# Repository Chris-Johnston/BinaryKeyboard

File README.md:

# BinaryKeyboard
A two-button backlit mechanical keyboard that types ASCII values, one bit at a time.

## Photos

## GIFS

Typing the backspace character, followed by switching between modes.

Demonstrating left to right input.

New animations added to '1/0' mode. (Still working on a name for that).

Demonstrating compatibility with USB OTG.

Boot up sequence.

Demonstrating right to left input.

Demonstrating switching between typing modes.

Close-up of the blue led backlit keys.

# Technical Info

## Schematic

## Components
- Arduino Pro Micro (knockoff) [AliExpress - $3](https://www.aliexpress.com/store/product/Free-Shipping-New-Pro-Micro-for-arduino-ATmega32U4-5V-16MHz-Module-with-2-row-pin-header/318950_1348800135.html)
- Cherry MX Clear PCB Mount Mechanical Switches [MechanicalKeyboards.com - $10, w/ bulk pricing options](https://mechanicalkeyboards.com/shop/index.php?l=product_detail&p=594)
- SSD1306 OLED Display [AliExpress - $2.72](https://www.aliexpress.com/item/Wholesale-0-96-inch-4pin-White-OLED-Module-SSD1306-Drive-IC-128-64-I2C-IIC-Communication/32658908775.html?ws_ab_test=searchweb0_0,searchweb201602_4_10152_10065_10151_10068_10130_10136_10137_10060_10138_10155_10062_10156_10154_10056_10055_10054_10059_10099_10103_10102_10096_10148_10147_10052_10053_10142_10107_10050_10051_10084_10083_10080_10082_10081_10178_10110_10111_10112_10113_10114_10181_10037_10078_10079_10077_10073_10070_10123_10124,searchweb201603_1,afswitch_1,ppcSwitch_3&btsid=055812c7-c728-4744-bd70-e33da76f8242&algo_expid=f8fb9ab1-cd07-4575-a544-a11a33f28421-2&algo_pvid=f8fb9ab1-cd07-4575-a544-a11a33f28421)
- Blue 2 * 3 * 4 mm LEDs [AliExpress - $2.29 / 100ct](https://www.aliexpress.com/item/EC-Buying-100pcs-2X3X4-LED-Blue-Transparent-DC-Rectangle-LED-Light-Emitting-Diode-2-3-4/32806132582.html?ws_ab_test=searchweb0_0,searchweb201602_4_10152_10065_10151_10068_10130_10136_10137_10060_10138_10155_10062_10156_10154_10056_10055_10054_10059_10099_10103_10102_10096_10148_10147_10052_10053_10142_10107_10050_10051_10084_10083_10080_10082_10081_10178_10110_10111_10112_10113_10114_10181_10037_10078_10079_10077_10073_10070_10123_10124,searchweb201603_1,afswitch_1,ppcSwitch_3&btsid=54ec29ec-c549-4d5f-a95b-290ab57c28c5&algo_expid=802203e6-7262-45b3-bbf0-e52533f80bf5-0&algo_pvid=802203e6-7262-45b3-bbf0-e52533f80bf5)

## Arduino Library Requirements
These libraries are used to drive the SSD1306 OLED display.
- [Adafruit_GFX](https://github.com/adafruit/Adafruit-GFX-Library)
- [Adafruit_SSD1306](https://github.com/adafruit/Adafruit_SSD1306)

## Eagle Schematic Details
Because I could not locate a part to represent the SSD1306 OLED Display, I created my own. This can be found in the
`CSJ Library` file for Eagle. A word of warning, this was my first time using Eagle. The part works, but could be improved.

Uses [c0z3n/cherrymx-eagle](https://github.com/c0z3n/cherrymx-eagle/) library as well.

## Usage
Each byte can either be typed from most significant bit to least significant bit (left to right), or least significant bit to most significant bit (right to left). This is configured before compiling and uploading to the board.
After all 8 bits have been entered, it will type out the ASCII value equivalent of that binary value. The Pro Micro has USB HID support,
which means it acts just like any other keyboard.

If both keys are held down, the keyboard will switch to "1/0 mode" / "single button press mode" (I'm bad at names).
In this mode, each key will represent a '1' or a '0' just like on a traditional keyboard, no binary involved.

## Arduino Problems
Initially I was going to use a [DigiStump](http://digistump.com/products/1) board for this, but I found issues with not having enough memory to work with after importing libraries and not enough I/O. I'm using an Arduino Pro Micro knockoff. The reason that there is electrical tape covering it is because I found that shorting the contacts with a finger would cause it to stop working. I'm still not really sure why.

### Keyboard Class Limitations
This project relies on the Arduino Keyboard library to handle all USB HID support.
It works great for printing standard characters and most operations, however, a downside of using this means that
not all ASCII values are supported. [Most of the values below `0x20` are not actually supported.](https://github.com/arduino-libraries/Keyboard/blob/master/src/Keyboard.cpp#L88)

User [dtwilliamson](https://github.com/dtwilliamson) [added a feature](https://github.com/Chris-Johnston/BinaryKeyboard/pull/5) that repurposes these values as control commands.
[Here is a list of some control key commands](https://en.wikipedia.org/wiki/Control_key#Examples).

The functionality of Backspace, Tab, and Enter is still preserved by setting `HID_MODE` to `true`.

| Binary     | `HID_MODE false` | `HID_MODE true` |
| ---------- | ---------------- | --------------- |
| `00000001` | `L_CTRL + A`     | `L_CTRL + A`    |
| `00000010` | `L_CTRL + B`     | `L_CTRL + B`    |
| `00001000` | `L_CTRL + H`     | `Backspace`     |
| `00001001` | `L_CTRL + I`     | `Tab`           |
| `00001010` | `L_CTRL + J`     | `Enter`         |
| `00100000` | ` ` (whitespace) | ` ` (whitespace)|
| `00100001` | `!`              | `!`             |
| `01100001` | `a`              | `a`             |
| `01000001` | `A`              | `A`             |

Note that CTRL+H, CTRL+I, and CTRL+J function the same in a Unix command line as the keys do. Up to you which setting to use. `HID_MODE true` works just fine in Windows and the GNOME desktop environment.

# Contribution and Modifications
Please feel free to fork this project for your own purposes. If you build one, I would love to see it!

If you have suggestions/improvements/feedback/bug reports/etc., submitting a pull request or an issue through GitHub is the best way to contribute.

# Acknowledgments
Special thanks goes to everyone in the UWB Makerspace that helped make this possible.

Pixel art for screen animations by [@Omrii_](https://twitter.com/omrii_) https://github.com/OmriN7.

Please see the [Binary Keyboard contributors page](https://github.com/Chris-Johnston/BinaryKeyboard/graphs/contributors) for a list of contributors. Many thanks to each of you for your support!

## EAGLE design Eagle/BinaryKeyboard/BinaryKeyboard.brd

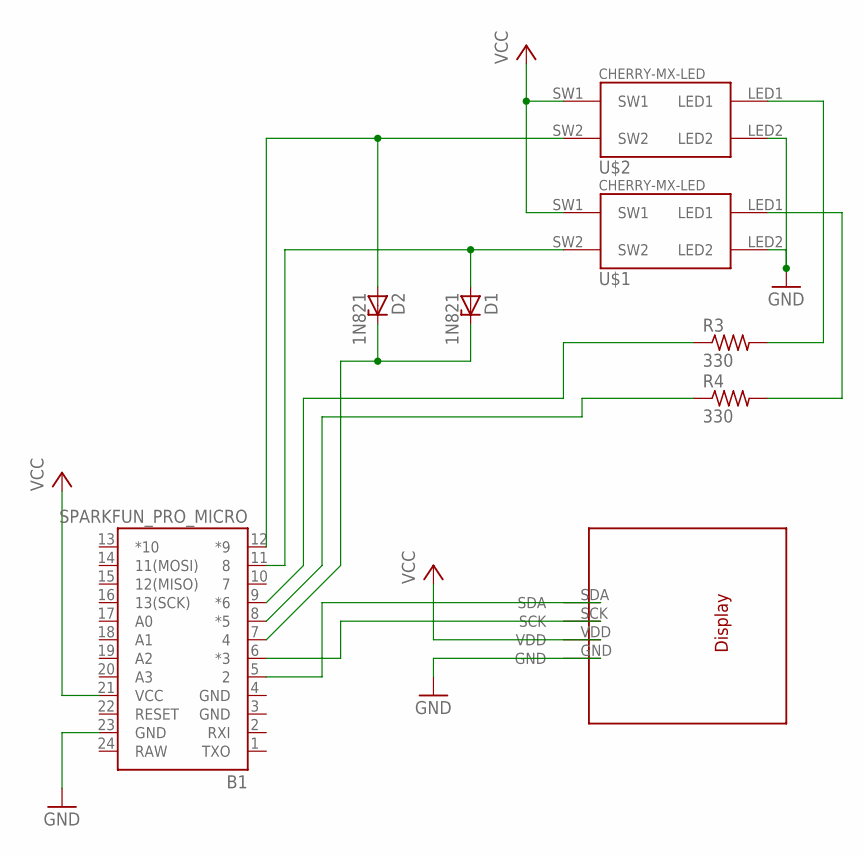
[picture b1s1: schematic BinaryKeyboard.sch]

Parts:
B1: SPARKFUN_PRO_MICRO
D1, D2: 1N821; DO35Z10
DISPLAY1: GM009605
R3, R4: 330; 0204/7
U$1, U$2: CHERRY-MX-LED

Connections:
GND: B1.3 (GND), B1.4 (GND), B1.23 (GND), DISPLAY1.GND, U$1.LED2, U$2.LED2
unnamed: B1.11 (8), D1.A, U$1.SW2
unnamed: B1.12 (*9), D2.A, U$2.SW2
unnamed: B1.5 (2), DISPLAY1.SDA
unnamed: B1.6 (*3), DISPLAY1.SCK
unnamed: R3.2, U$2.LED1
unnamed: R4.2, U$1.LED1
unnamed: B1.9 (*6), R3.1
unnamed: B1.8 (*5), R4.1
unnamed: B1.7 (4), D1.C, D2.C
RAW: B1.24 (RAW)
VCC: B1.21 (VCC), DISPLAY1.VDD, U$1.SW1, U$2.SW1

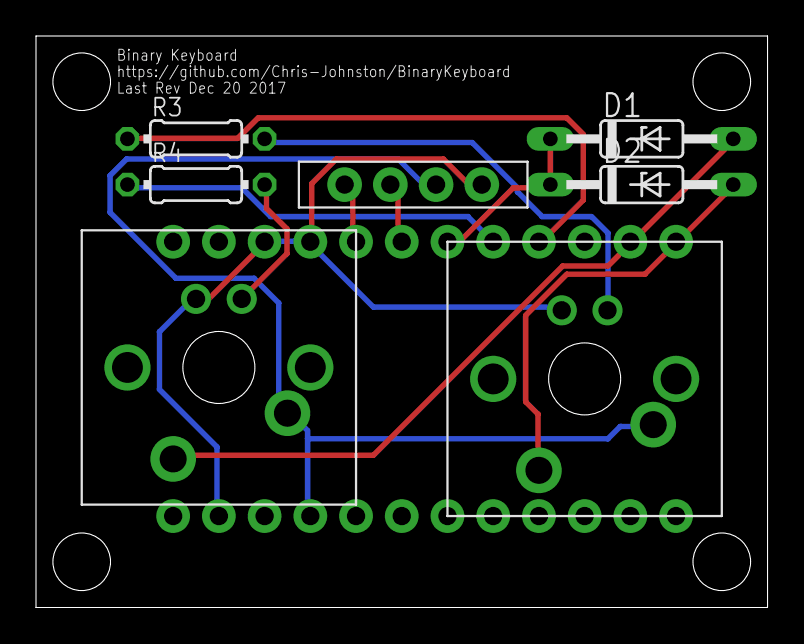
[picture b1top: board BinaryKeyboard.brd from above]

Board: 2 copper layers, 40.6 x 31.8 mm, 8 parts (1 on the bottom side), 11 nets.

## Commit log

2017-04-14 Added schematic, screenshots, major updates to code
2017-04-14 LICENSE.txt
2017-04-14 Added images
2017-04-14 Renamed and moved files
2017-04-14 Added images and gifs to README
    Time for sleep now.
2017-04-19 Added Right-to-left / Left-to-Right flag. Adjusted boot animation text.
    For those who requested being able to type the other way.
2017-04-19 Adjusted wording of Usage. Fix #1. for 8c62b70
    It was late when I wrote that. Explained setting RTL/LTR mode.
2017-04-20 Minor spelling corrections
2017-04-20 Added more gifs to readme
    Demonstrates different methods of input, USB OTG compatibility
2017-04-22 Fix #4. Elaborated on part sources, provided links
    Added links to where I bought each component. Included price at the time of writing.
2017-04-22 Added animations and usage tweaks to 1/0 mode.
    Special thanks to https://twitter.com/omrii_ https://github.com/OmriN7
    for providing the pixel art.
    Now this is where I ask myself if I have gone too far.
    The answer is no.
    I have not.
2017-04-22 Trying to update .gitattributes
2017-04-22 Moved Eagle specific files into Eagle folder
    Also removed tracking of Eagle files as overall project
2017-04-25 fix line endings
2017-04-25 add ability to output control characters ASCII < 0x20
2017-04-26 Updated .gitattributes to support autocrlf
    reference: https://git-scm.com/docs/gitattributes
2017-04-26 adjusted .gitattributes for more consistent line endings
2017-04-26 End-of-line normalization, see dtwilliamson:ctrl 6335dcc
2017-04-26 Added credit for pixel art to README
    Contributor sent these files to me directly and did not collaborate through git.
2017-04-27 output ctrl char representation to display
2017-04-27 add HID output mode
2017-04-27 fix missing paren
2017-04-27 correct logic in display of ctrl chars
2017-04-28 Added comments. Defined constants. Separated debounce timers. Added flag to disable switching.
    I am more than guilty of doing too much in a single commit.
    Added a ton of comments so that newbies might get it.
    Changed variables that were used as constant to just be #define 'd
    instead. No more magic #s?
    For some reason I was using a single debounce timer for both buttons.
    Fixed. In addition added debounce to single button press mode.
2017-04-28 Updated README w/ control character stuff
    Minor changes to contributor info
2017-04-28 revised comments and readme regarding control character letter case
2017-04-28 Changed README ctrl char representation back
    For display purposes, ctrl characters should be uppercase. In the implementation they should be treated as lowercase (because of Keyboard lib implementation).
2017-05-10 Fixed held buttons on switching modes
    previously, one button may have been held down when modes are switched
2017-12-21 re-organized directory structure
2017-12-21 modified the arduino firmware to use diodes instead of resistors
2017-12-21 Added new board files

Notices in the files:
parts and their libraries:
SparkFun-Boards: Licensing: Creative Commons ShareAlike 4.0 International - https://creativecommons.org/licenses/by-sa/4.0
